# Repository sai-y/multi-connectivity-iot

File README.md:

# multi-connectivity-iot
Repo for multi-connectivity hardware design

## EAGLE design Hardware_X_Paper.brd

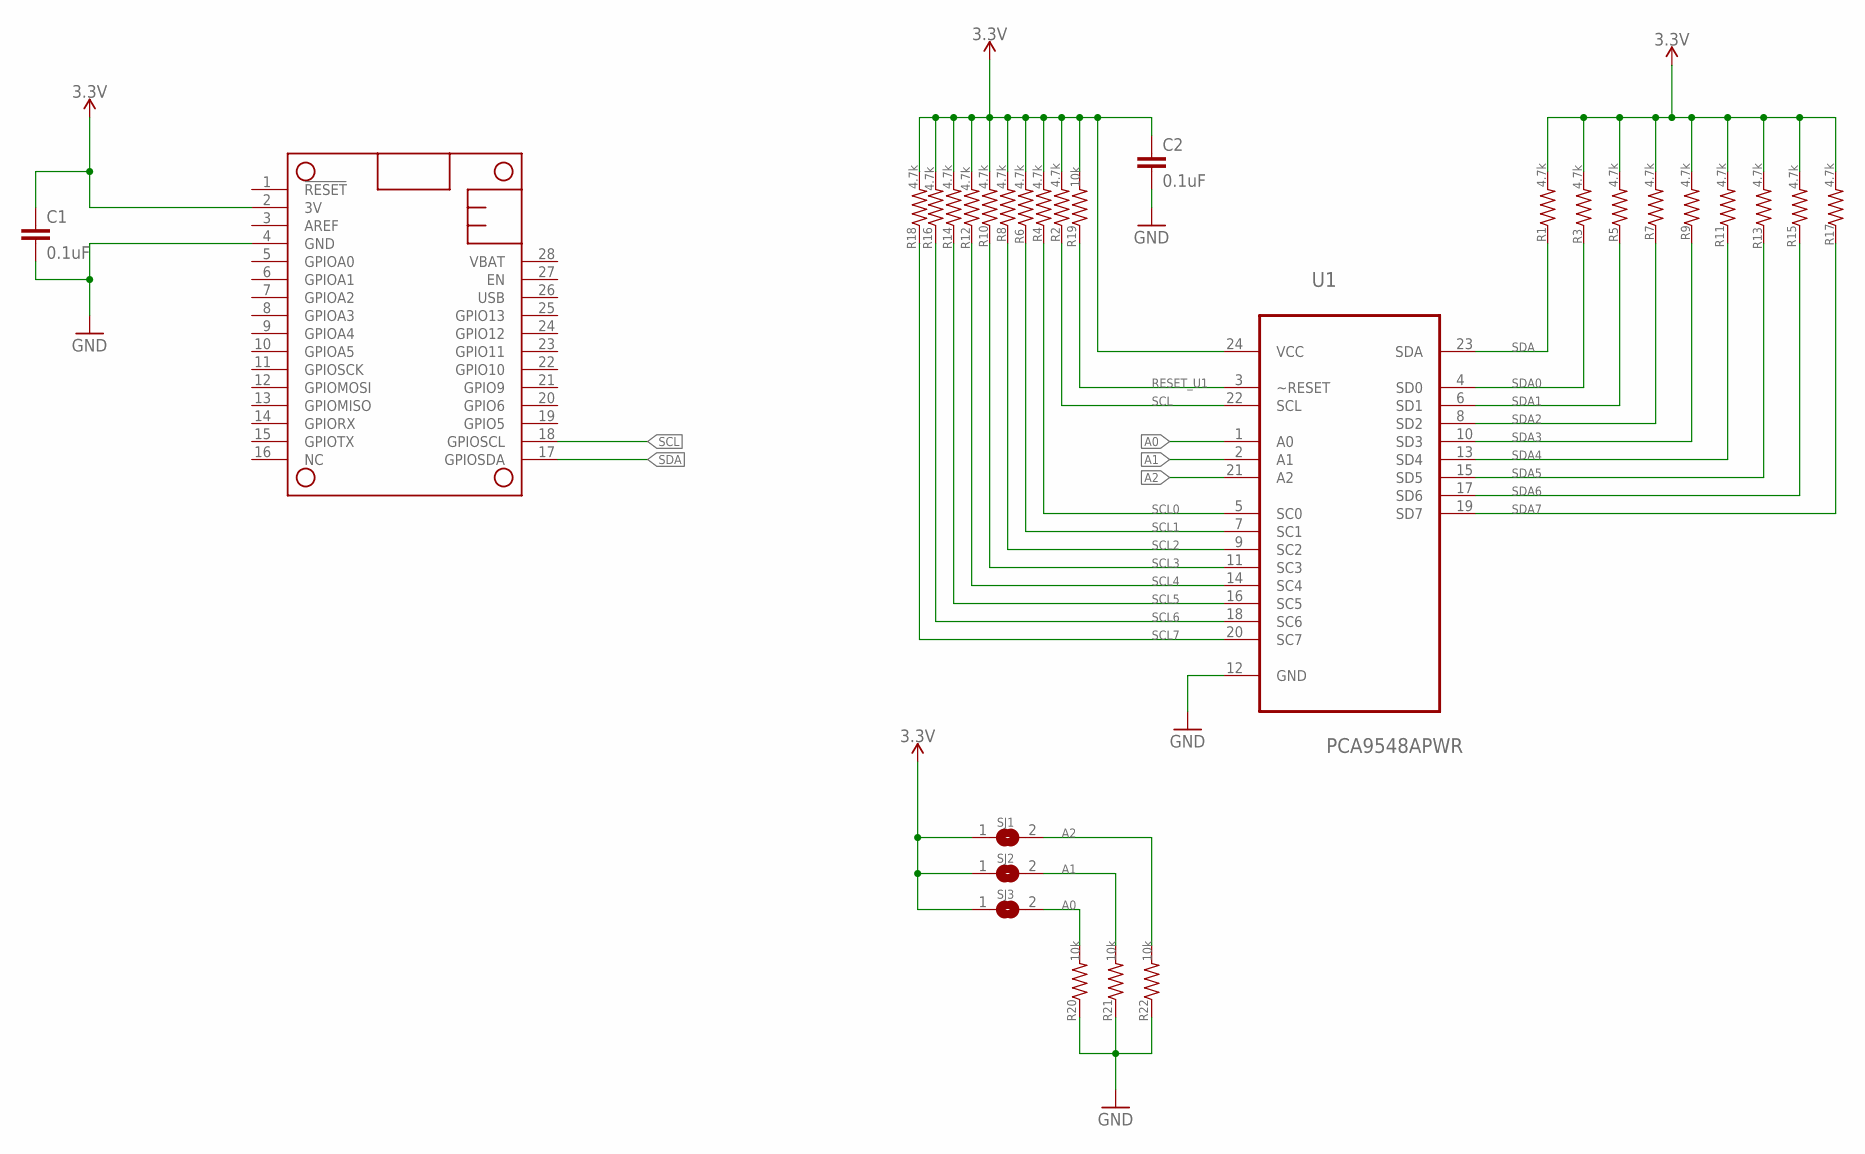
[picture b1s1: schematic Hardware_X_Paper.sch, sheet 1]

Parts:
C1, C2: 0.1uF; 0603
MS1: MICROBUILDER_FEATHERWING_NOHOLES
R1, R2, R3, R4, R5, R6, R7, R8, R9, R10, R11, R12, R13, R14, R15, R16, R17, R18: 4.7k; 0603
R19, R20, R21, R22: 10k; 0603
SJ1, SJ2, SJ3: MICROBUILDER_SOLDERJUMPER; MICROBUILDER_SOLDERJUMPER_ARROW_NOPASTE
U1: PCA9548APWR; SOP65P640X120-24N

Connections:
3.3V: C1.1, C2.1, MS1.2 (3V), R1.2, R2.2, R3.2, R4.2, R5.2, R6.2, R7.2, R8.2, R9.2, R10.2, R11.2, R12.2, R13.2, R14.2, R15.2, R16.2, R17.2, R18.2, R19.2, SJ1.1, SJ2.1, SJ3.1, U1.24 (VCC); also elsewhere on the board
A0: R20.2, SJ3.2, U1.1 (A0)
A1: R21.2, SJ2.2, U1.2 (A1)
A2: R22.2, SJ1.2, U1.21 (A2)
GND: C1.2, C2.2, MS1.4 (GND), R20.1, R21.1, R22.1, U1.12 (GND); also elsewhere on the board
RESET_U1: R19.1, U1.3 (~RESET)
SCL: MS1.18 (GPIOSCL), R2.1, U1.22 (SCL)
SCL0: R4.1, U1.5 (SC0); also elsewhere on the board
SCL1: R6.1, U1.7 (SC1); also elsewhere on the board
SCL2: R8.1, U1.9 (SC2); also elsewhere on the board
SCL3: R10.1, U1.11 (SC3); also elsewhere on the board
SCL4: R12.1, U1.14 (SC4); also elsewhere on the board
SCL5: R14.1, U1.16 (SC5); also elsewhere on the board
SCL6: R16.1, U1.18 (SC6); also elsewhere on the board
SCL7: R18.1, U1.20 (SC7); also elsewhere on the board
SDA: MS1.17 (GPIOSDA), R1.1, U1.23 (SDA)
SDA0: R3.1, U1.4 (SD0); also elsewhere on the board
SDA1: R5.1, U1.6 (SD1); also elsewhere on the board
SDA2: R7.1, U1.8 (SD2); also elsewhere on the board
SDA3: R9.1, U1.10 (SD3); also elsewhere on the board
SDA4: R11.1, U1.13 (SD4); also elsewhere on the board
SDA5: R13.1, U1.15 (SD5); also elsewhere on the board
SDA6: R15.1, U1.17 (SD6); also elsewhere on the board
SDA7: R17.1, U1.19 (SD7); also elsewhere on the board

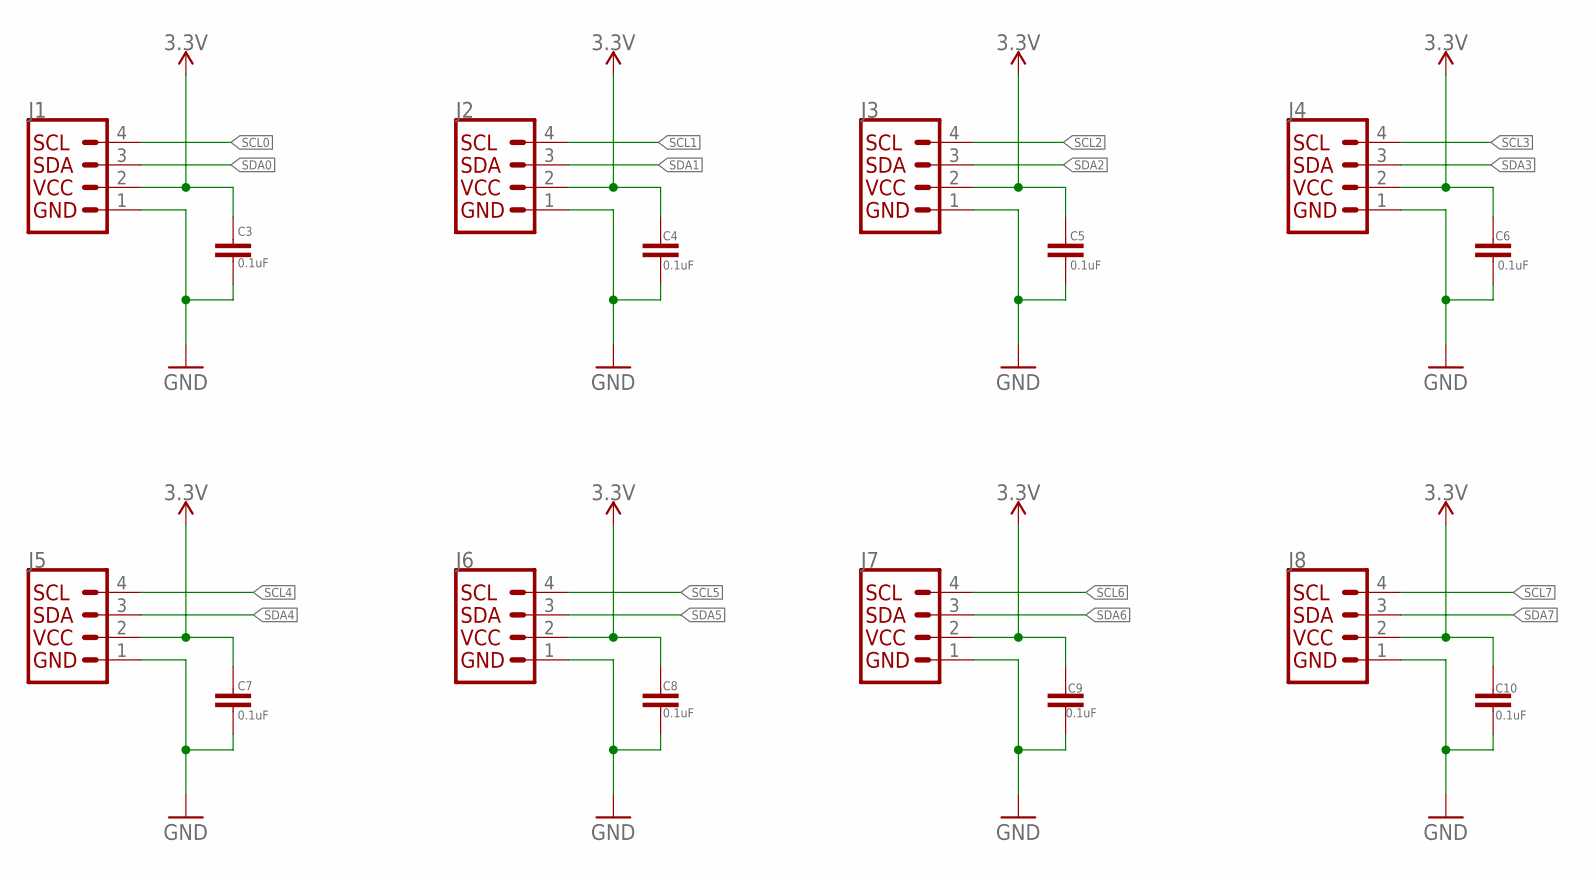
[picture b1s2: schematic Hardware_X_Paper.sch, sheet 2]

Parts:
C3, C4, C5, C6, C7, C8, C9, C10: 0.1uF; 0603
J1, J2, J3, J4, J5, J6, J7, J8: QWIIC_CONNECTORJS-1MM; 1X04_1MM_RA

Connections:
3.3V: C3.1, C4.1, C5.1, C6.1, C7.1, C8.1, C9.1, C10.1, J1.2 (VCC), J2.2 (VCC), J3.2 (VCC), J4.2 (VCC), J5.2 (VCC), J6.2 (VCC), J7.2 (VCC), J8.2 (VCC); also elsewhere on the board
GND: C3.2, C4.2, C5.2, C6.2, C7.2, C8.2, C9.2, C10.2, J1.1 (GND), J2.1 (GND), J3.1 (GND), J4.1 (GND), J5.1 (GND), J6.1 (GND), J7.1 (GND), J8.1 (GND); also elsewhere on the board
SCL0: J1.4 (SCL); also elsewhere on the board
SCL1: J2.4 (SCL); also elsewhere on the board
SCL2: J3.4 (SCL); also elsewhere on the board
SCL3: J4.4 (SCL); also elsewhere on the board
SCL4: J5.4 (SCL); also elsewhere on the board
SCL5: J6.4 (SCL); also elsewhere on the board
SCL6: J7.4 (SCL); also elsewhere on the board
SCL7: J8.4 (SCL); also elsewhere on the board
SDA0: J1.3 (SDA); also elsewhere on the board
SDA1: J2.3 (SDA); also elsewhere on the board
SDA2: J3.3 (SDA); also elsewhere on the board
SDA3: J4.3 (SDA); also elsewhere on the board
SDA4: J5.3 (SDA); also elsewhere on the board
SDA5: J6.3 (SDA); also elsewhere on the board
SDA6: J7.3 (SDA); also elsewhere on the board
SDA7: J8.3 (SDA); also elsewhere on the board

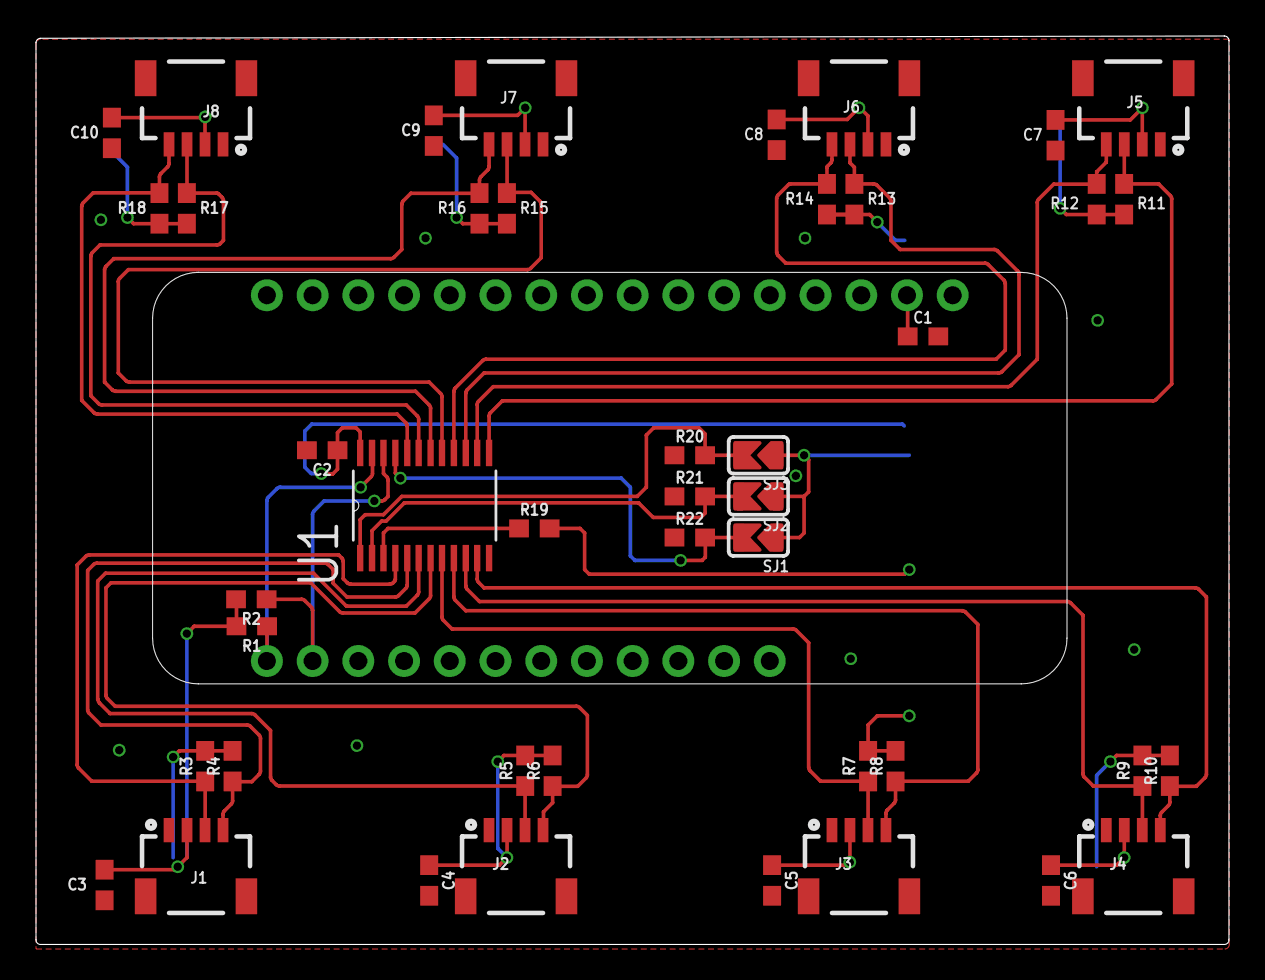
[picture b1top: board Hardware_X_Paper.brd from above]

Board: 2 copper layers, 66.3 x 50.5 mm, 45 parts (0 on the bottom side), 24 nets.

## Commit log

2019-02-15 Hardware repo

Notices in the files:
parts and their libraries:
SparkFun-Resistors: Licensing: Creative Commons ShareAlike 4.0 International - https://creativecommons.org/licenses/by-sa/4.0
